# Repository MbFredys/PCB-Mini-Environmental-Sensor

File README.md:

# PCB-Mini-Environmental-Sensor

This is a compact environmental monitoring PCB design that enables precise tracking of multiple atmospheric parameters with the following features:

1. 🌡️ Monitors temperature, humidity, and atmospheric pressure using BME280 sensor
2. 💨 Measures air quality and CO2 equivalent with Sensirion SPG40 sensor
3. 📶 WiFi and Bluetooth connectivity via ESP32-C3-VROOM-02 microcontroller
4. 🔋 Battery-powered operation with 3.7V Li-ion battery and USB-C charging
5. ⚡ Efficient power management using TPS62203 step-down converter
6. 🔄 Automatic data logging with cloud connectivity capabilities
7. 💤 Ultra-low power consumption with deep sleep mode
8. 🌧️ Weather-resistant design suitable for indoor and outdoor use

# Usage
To use the environmental sensor node, follow these steps:

  1. Power the device using either the 3.7V battery or USB-C connection
  2. Place the sensor in your desired monitoring location (indoor or outdoor)
  3. Connect to WiFi using the device's configuration interface
  4. Monitor environmental data in real-time through the web dashboard
  5. Analyze historical trends
  6. Receive alerts when environmental parameters exceed safe levels

The device automatically optimizes power consumption by entering deep sleep between measurements, ensuring extended battery life while providing continuous environmental monitoring for smart home, agricultural, and industrial applications.

# Getting Started
To get started with the Environmental Sensor Node PCB design, follow these steps:

  1. Clone this repository to your local machine
  2. Open the PCB design files in your preferred EDA software (KiCAD recommended)
  3. Review the schematic and layout - pay special attention to:
  4. RF antenna keep-out zone for ESP32-C3
  5. I2C routing between sensors and microcontroller
  6. Power distribution network
  7. Send the files to PCBWay for professional fabrication

# Hardware Setup
After receiving your PCBs, solder components in this recommended order:

  1. Power section (TPS62203, MCP73831)
  2. ESP32-C3 module
  3. Sensors (BME280, SPG40)
  4. Passive components and connectors
  5. Program the ESP32-C3 via USB-C connection
  6. Connect a 3.7V Li-ion battery to the battery connector
  7. Test each sensor

# Contributing
If you would like to contribute to the Environmental Sensor Node project, please follow these steps:

  1. Fork this repository
  2. Create a feature branch (git checkout -b feature/improvement)
  3. Make your enhancements - consider:
  4. Power optimization techniques
  5. Additional sensor support
  6. Improved enclosure designs
  7. Localization for different regions
  8. Test your changes thoroughly
  9. Submit a pull request with detailed description

# Areas for Contribution
1. 🔋 Power management algorithms
2. 📡 Wireless protocol optimizations
3. 🌡️ Sensor calibration procedures
4. 🏠 Enclosure designs for different environments
5. 📊 Data visualization interfaces
6. 🔧 Manufacturing improvements

# License
This project is licensed under the CERN Open Hardware Licence Version 2 - Weakly Reciprocal (CERN-OHL-W-2.0).
See the [CERN-OHL-W-2.0 ↗](https://gitlab.com/ohwr/project/cernohl/-/wikis/uploads/82b567f43ce515395f7ddbfbad7a8806/cern_ohl_w_v2.txt) file for more information.

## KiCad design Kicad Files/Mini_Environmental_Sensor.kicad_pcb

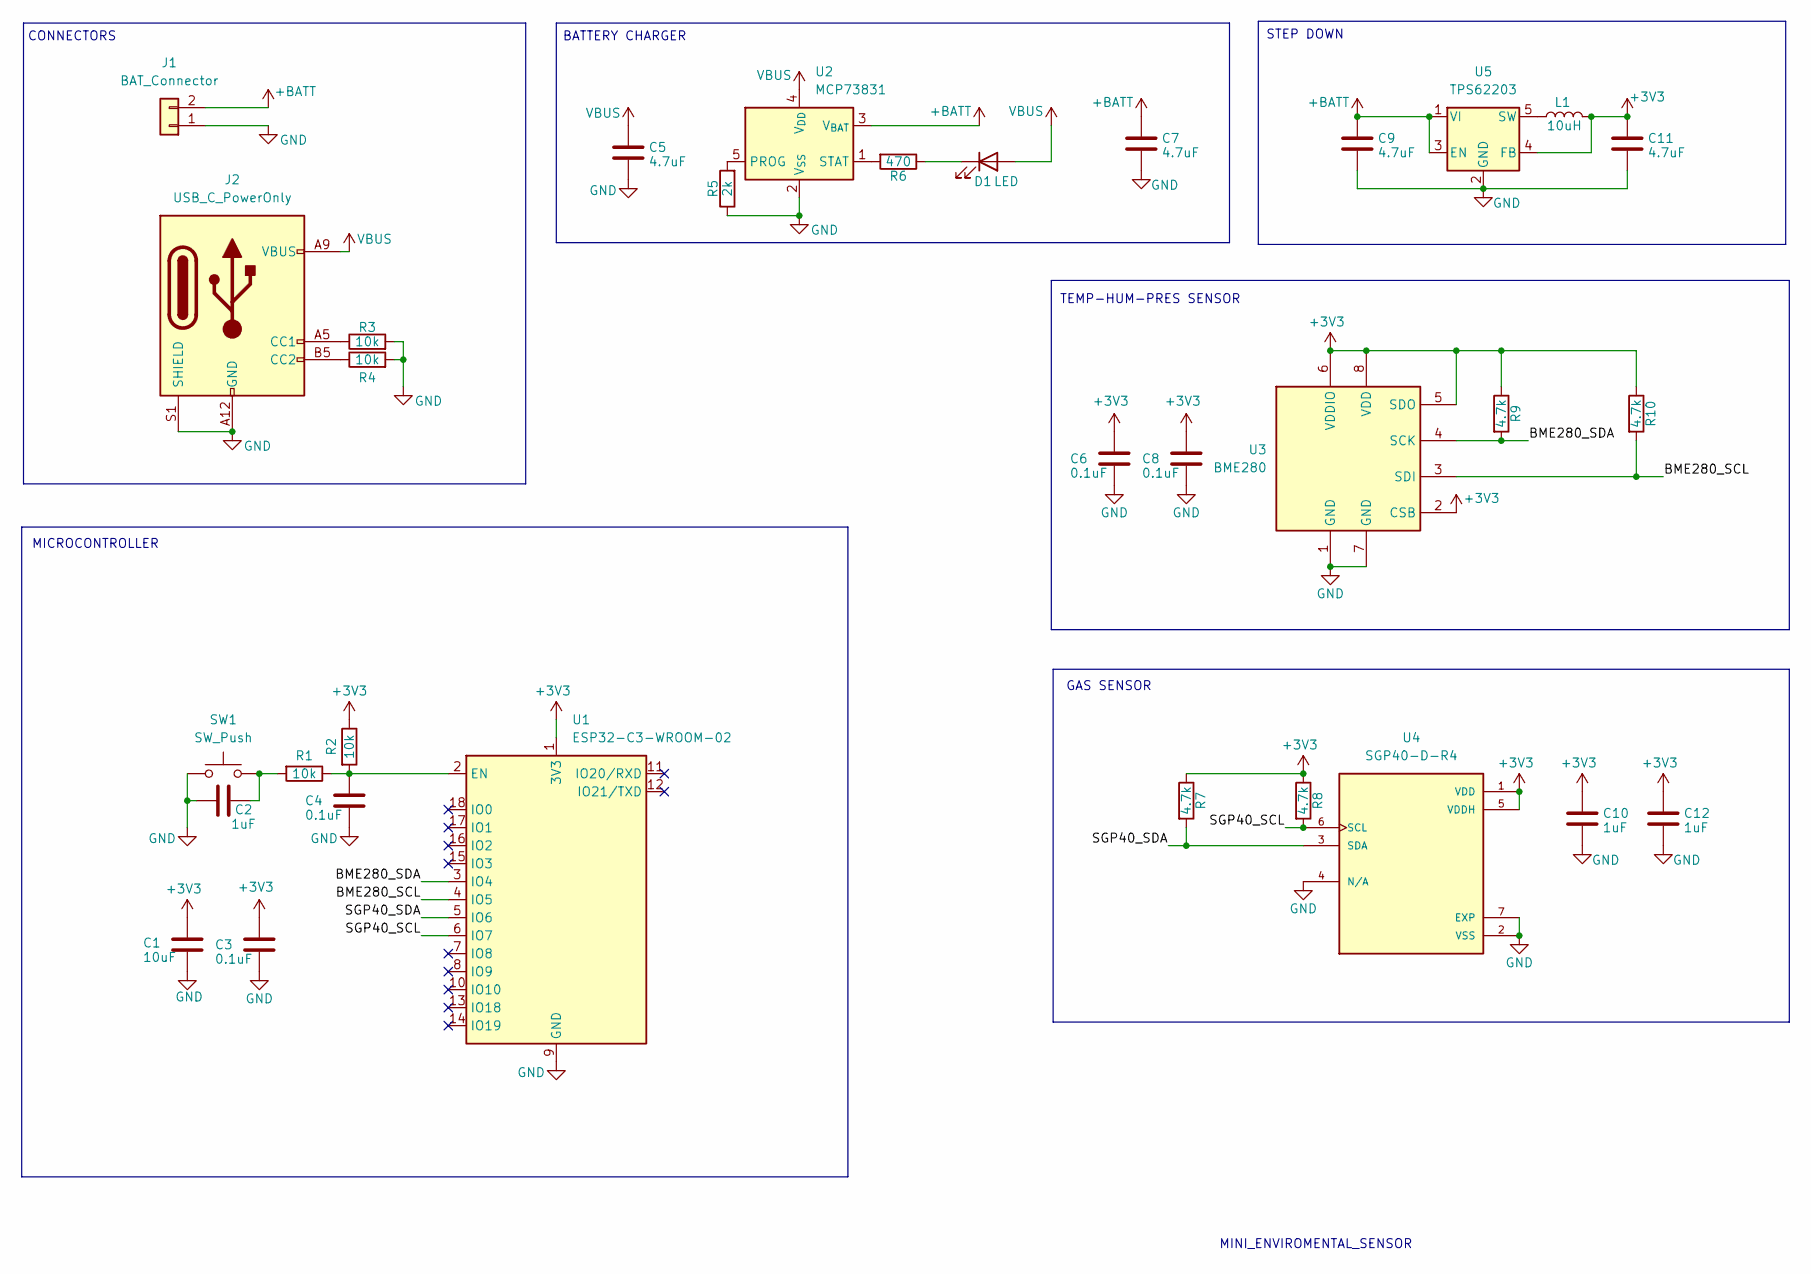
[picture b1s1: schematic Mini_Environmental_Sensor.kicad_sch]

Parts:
C1: 10uF; C_0603_1608Metric; MPN CL10A106KP8NNNC; LCSC PN C19702
C2, C10, C12: 1uF; C_0603_1608Metric; MPN SMDTC04100VA00MS00; LCSC PN C29266
C3, C4, C6, C8: 0.1uF; C_0402_1005Metric; MPN CL05B104KO5NNNC; LCSC PN C1525
C5, C7, C9, C11: 4.7uF; C_0603_1608Metric; MPN CL10A475KP8NNNC; LCSC PN C1705
D1: LED; LED_0603_1608Metric
J1: BAT_Connector; Molex_PicoBlade_53261-0271_1x02-1MP_P1.25mm_Horizontal; MPN 532610271; LCSC PN C177225
J2: USB_C_PowerOnly; USB_C_Receptacle_GCT_USB4135-GF-A_6P_TopMnt_Horizontal; MPN USB4135-GF-A; LCSC PN C5438410
L1: 10uH; L_0603_1608Metric
R1, R2, R3, R4: 10k; R_0603_1608Metric; MPN RC0603FR-0710KL; LCSC PN C98220
R5: 2k; R_0603_1608Metric; MPN RC0603FR-072KL; LCSC PN C105576
R6: 470; R_0402_1005Metric; MPN 0402WGF4700TCE; LCSC PN C25117
R7, R8, R9, R10: 4.7k; R_0603_1608Metric; MPN RC0603FR-074K7L; LCSC PN C99782
SW1: SW_Push; SW_Push_SPST_NO_Alps_SKRK; MPN SKRKAEE020; LCSC PN C115357
U1: ESP32-C3-WROOM-02; MPN ESP32-C3-WROOM-02-N4; LCSC PN C2934560
U2: MCP73831; SOT-23-5; MPN MCP73831T-2ACI/OT; LCSC PN C424093
U3: BME280; Bosch_LGA-8_2.5x2.5mm_P0.65mm_ClockwisePinNumbering; MPN BME280; LCSC PN C92489
U4: SGP40-D-R4; XCDR_SGP40-D-R4; MPN SGP40-D-R4
U5: TPS62203; SOT-23-5; MPN TPS62203DBVR; LCSC PN C9051

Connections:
+3V3: C1.1, C3.1, C6.1, C8.1, C10.1, C11.1, C12.1, L1.2, R2.1, R7.1, R8.1, R9.1, R10.1, U1.1 (3V3), U3.2 (CSB), U3.5 (SDO), U3.6 (VDDIO), U3.8 (VDD), U4.1 (VDD), U4.5 (VDDH), U5.4 (FB)
+BATT: C7.1, C9.1, J1.2, U2.3 (V_{BAT}), U5.1 (VI), U5.3 (EN)
/BME280_SCL: R10.2, U1.4 (IO5), U3.3 (SDI)
/BME280_SDA: R9.2, U1.3 (IO4), U3.4 (SCK)
/SGP40_SCL: R8.2, U1.6 (IO7), U4.6 (SCL)
/SGP40_SDA: R7.2, U1.5 (IO6), U4.3 (SDA)
GND: C1.2, C2.2, C3.2, C4.2, C5.2, C6.2, C7.2, C8.2, C9.2, C10.2, C11.2, C12.2, J1.1, J2.A12 (GND), J2.B12 (GND), J2.S1 (SHIELD), R3.2, R4.2, R5.1, SW1.1, U1.9 (GND), U1.19 (GND), U2.2 (V_{SS}), U3.1 (GND), U3.7 (GND), U4.2 (VSS), U4.4 (N/A), U4.7 (EXP), U5.2 (GND)
unnamed: C2.1, R1.2, SW1.2
unnamed: D1.1 (K), R6.1
unnamed: J2.A5 (CC1), R3.1
unnamed: J2.B5 (CC2), R4.1
unnamed: C4.1, R1.1, R2.2, U1.2 (EN)
unnamed: R5.2, U2.5 (PROG)
unnamed: R6.2, U2.1 (STAT)
unnamed: L1.1, U5.5 (SW)
VBUS: C5.1, D1.2 (A), J2.A9 (VBUS), J2.B9 (VBUS), U2.4 (V_{DD})

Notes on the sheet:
MINI_ENVIROMENTAL_SENSOR
GAS SENSOR
BATTERY CHARGER
STEP DOWN
MICROCONTROLLER
CONNECTORS
TEMP-HUM-PRES SENSOR

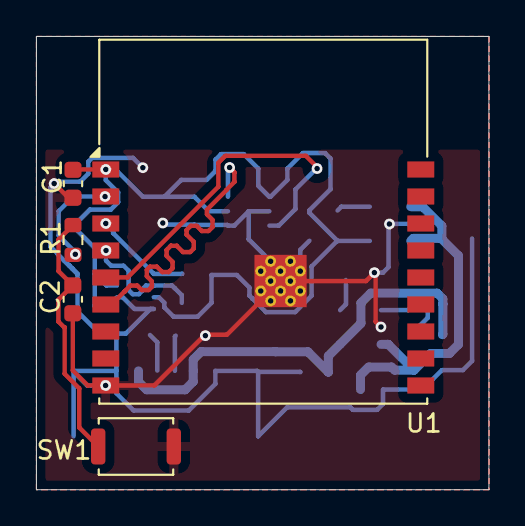
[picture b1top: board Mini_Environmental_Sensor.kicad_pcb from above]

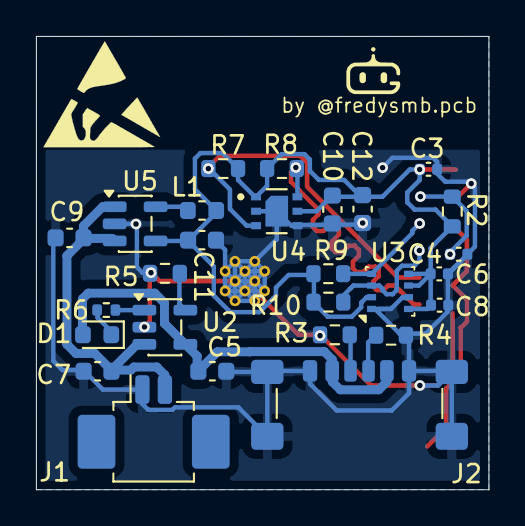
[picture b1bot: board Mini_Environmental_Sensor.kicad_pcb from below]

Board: 2 copper layers, 25.1 x 25.2 mm, 32 parts (27 on the bottom side), 16 nets.

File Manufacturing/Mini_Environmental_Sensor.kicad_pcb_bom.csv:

Designator,Quantity,Value,Footprint,Package,MPN,DNP,Mount_Type,Description,LCSC PN,Sim.Pins
C1,1,10uF,C_0603_1608Metric,0603,CL10A106KP8NNNC,,smt,Unpolarized capacitor,C19702,
"C10, C12, C2",3,1uF,C_0603_1608Metric,C20524683,SMDTC04100VA00MS00,,smt,Unpolarized capacitor,C29266,
"C11, C5, C7, C9",4,4.7uF,C_0603_1608Metric,0603,CL10A475KP8NNNC,,smt,Unpolarized capacitor,C1705,
"C3, C4, C6, C8",4,0.1uF,C_0402_1005Metric,0402,CL05B104KO5NNNC,,smt,Unpolarized capacitor,C1525,
D1,1,LED,LED_0603_1608Metric,,,,smt,Light emitting diode,,1=K 2=A
J1,1,BAT_Connector,Molex_PicoBlade_53261-0271_1x02-1MP_P1.25mm_Horizontal,"SMD,P=1.25mm,Surface Mount,Right Angle",532610271,,smt,"Generic connector, single row, 01x02, script generated (kicad-library-utils/schlib/autogen/connector/)",C177225,
J2,1,USB_C_PowerOnly,USB_C_Receptacle_GCT_USB4135-GF-A_6P_TopMnt_Horizontal,USB-C_6P_SMD,USB4135-GF-A,,smt,USB Power-Only 6P Type-C Receptacle connector,C5438410,
L1,1,10uH,L_0603_1608Metric,,,,smt,Inductor,,
"R1, R2, R3, R4",4,10k,R_0603_1608Metric,0603,RC0603FR-0710KL,,smt,Resistor,C98220,
"R10, R7, R8, R9",4,4.7k,R_0603_1608Metric,0603,RC0603FR-074K7L ,,smt,Resistor,C99782 ,
R5,1,2k,R_0603_1608Metric,0603,RC0603FR-072KL,,smt,Resistor,C105576,
R6,1,470,R_0402_1005Metric,0402,0402WGF4700TCE,,smt,Resistor,C25117,
SW1,1,SW_Push,SW_Push_SPST_NO_Alps_SKRK,"SMD,3.9x2.9mm",SKRKAEE020,,smt,"Push button switch, generic, two pins",C115357,
U1,1,ESP32-C3-WROOM-02,ESP32-C3-WROOM-02,VFQFN-32-EP,ESP32-C3-WROOM-02-N4,,smt,"802.11 b/g/n Wi­Fi and Bluetooth 5 module, ESP32­C3 SoC, RISC­V microprocessor, On-board antenna",C2934560,
U2,1,MCP73831,SOT-23-5,SOT-23-5,MCP73831T-2ACI/OT,,smt,"Single cell, Li-Ion/Li-Po charge management controller, 4.50V, Tri-State Status Output, in SOT23-5 package",C424093,
U3,1,BME280,Bosch_LGA-8_2.5x2.5mm_P0.65mm_ClockwisePinNumbering,  LGA-8(2.5x2.5) ,  BME280 ,,smt,"3-in-1 sensor, humidity, pressure, temperature, I2C and SPI interface, 1.71-3.6V, LGA-8",C92489,
U4,1,SGP40-D-R4,XCDR_SGP40-D-R4,DFN-4,SGP40-D-R4,,smt,,,
U5,1,TPS62203,SOT-23-5,SOT-23-5,TPS62203DBVR,,smt,"300mA High-Efficiency Step-Down DC-DC Converter, adjustable output voltage, 2.5-6V input voltage, SOT-23-5",  C9051 ,

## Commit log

2025-10-10 Update README.md
    This is the first README
2025-10-10 Create Firmware
2025-12-01 Change license to CERN-OHL-W v2
    Updated the license from MIT to CERN Open Hardware Licence Version 2 - Weakly Reciprocal.
2025-12-01 Add CERN Open Hardware Licence
    Added CERN Open Hardware Licence Version 2 - Weakly Reciprocal to the project.
2025-12-01 Change license to CERN-OHL-W-2.0
    Updated license information from MIT to CERN Open Hardware License Version 2.
2025-12-01 Fix license link in LICENSE file
    Updated the link to the CERN-OHL-W v2 license.

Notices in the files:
README.md:
License: CERN-OHL-W-2.0
